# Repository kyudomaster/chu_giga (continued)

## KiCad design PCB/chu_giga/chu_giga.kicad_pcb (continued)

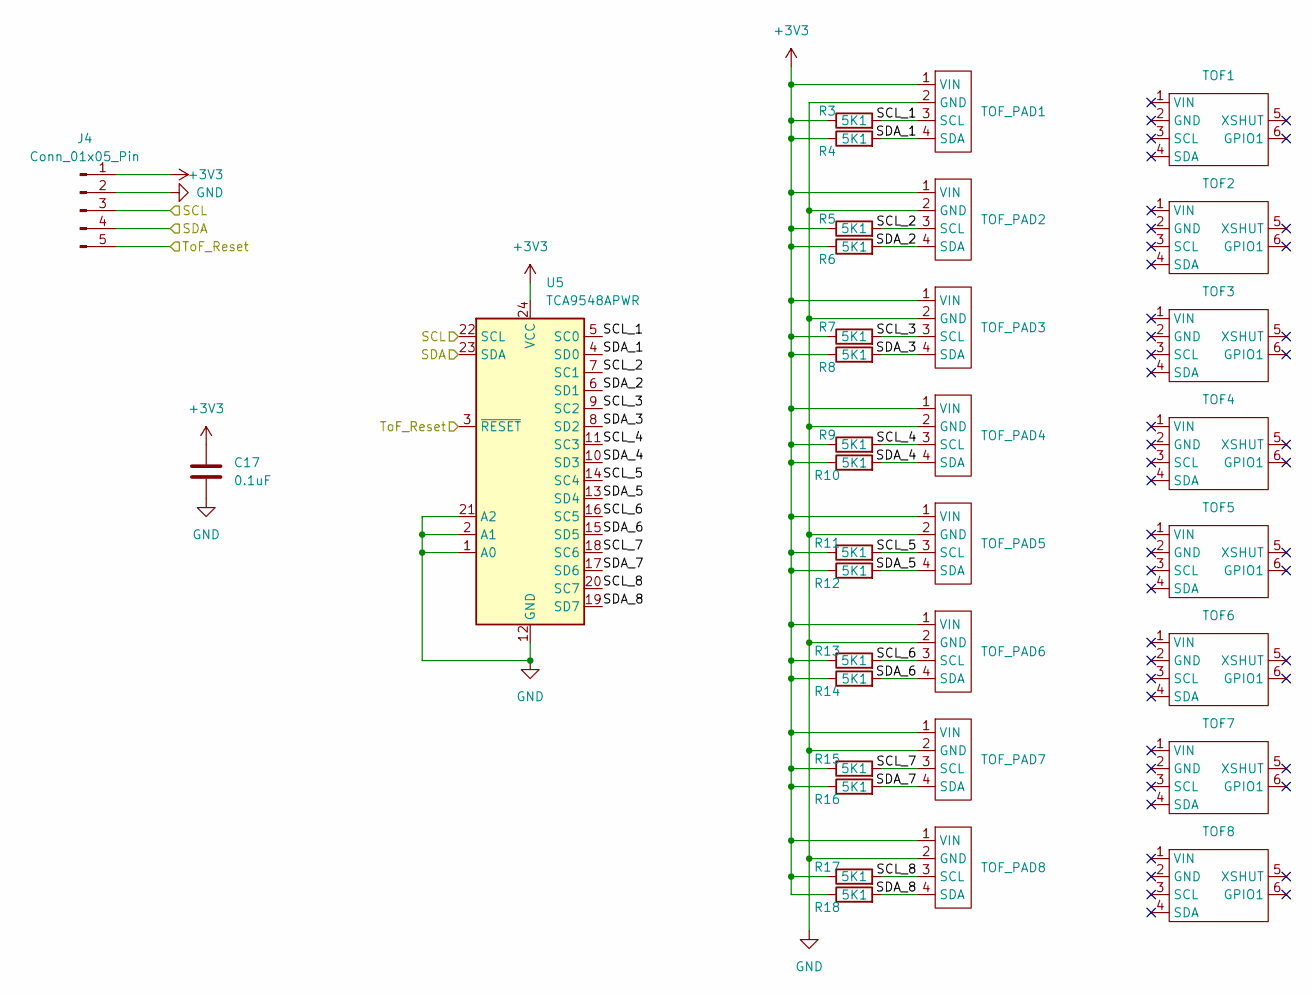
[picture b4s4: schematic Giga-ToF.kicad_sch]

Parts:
C17: 0.1uF; TMCP1E104MTRF
J4: Conn_01x05_Pin; 17754695
R3, R4, R5, R6, R7, R8, R9, R10, R11, R12, R13, R14, R15, R16, R17, R18: 5K1; R_0805_2012Metric_Pad1.20x1.40mm_HandSolder
TOF1, TOF2, TOF3, TOF4, TOF5, TOF6, TOF7, TOF8: GY530 ToF Sensor board
TOF_PAD1, TOF_PAD2, TOF_PAD3, TOF_PAD4, TOF_PAD5, TOF_PAD6, TOF_PAD7, TOF_PAD8: ToF Wiring Pad
U5: TCA9548APWR; SOP65P640X120-24N

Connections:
+3V3: C17.1, J4.1, R3.1, R4.1, R5.1, R6.1, R7.1, R8.1, R9.1, R10.1, R11.1, R12.1, R13.1, R14.1, R15.1, R16.1, R17.1, R18.1, TOF_PAD1.1 (VIN), TOF_PAD2.1 (VIN), TOF_PAD3.1 (VIN), TOF_PAD4.1 (VIN), TOF_PAD5.1 (VIN), TOF_PAD6.1 (VIN), TOF_PAD7.1 (VIN), TOF_PAD8.1 (VIN), U5.24 (VCC); also elsewhere on the board
/Controller/SCL: J4.3, U5.22 (SCL); also elsewhere on the board
/Controller/SDA: J4.4, U5.23 (SDA); also elsewhere on the board
/Controller/ToF_Reset: J4.5, U5.3 (~RESET); also elsewhere on the board
/Time-Of-Flight sensors/SCL_1: R3.2, TOF_PAD1.3 (SCL), U5.5 (SC0)
/Time-Of-Flight sensors/SCL_2: R5.2, TOF_PAD2.3 (SCL), U5.7 (SC1)
/Time-Of-Flight sensors/SCL_3: R7.2, TOF_PAD3.3 (SCL), U5.9 (SC2)
/Time-Of-Flight sensors/SCL_4: R9.2, TOF_PAD4.3 (SCL), U5.11 (SC3)
/Time-Of-Flight sensors/SCL_5: R11.2, TOF_PAD5.3 (SCL), U5.14 (SC4)
/Time-Of-Flight sensors/SCL_6: R13.2, TOF_PAD6.3 (SCL), U5.16 (SC5)
/Time-Of-Flight sensors/SCL_7: R15.2, TOF_PAD7.3 (SCL), U5.18 (SC6)
/Time-Of-Flight sensors/SCL_8: R17.2, TOF_PAD8.3 (SCL), U5.20 (SC7)
/Time-Of-Flight sensors/SDA_1: R4.2, TOF_PAD1.4 (SDA), U5.4 (SD0)
/Time-Of-Flight sensors/SDA_2: R6.2, TOF_PAD2.4 (SDA), U5.6 (SD1)
/Time-Of-Flight sensors/SDA_3: R8.2, TOF_PAD3.4 (SDA), U5.8 (SD2)
/Time-Of-Flight sensors/SDA_4: R10.2, TOF_PAD4.4 (SDA), U5.10 (SD3)
/Time-Of-Flight sensors/SDA_5: R12.2, TOF_PAD5.4 (SDA), U5.13 (SD4)
/Time-Of-Flight sensors/SDA_6: R14.2, TOF_PAD6.4 (SDA), U5.15 (SD5)
/Time-Of-Flight sensors/SDA_7: R16.2, TOF_PAD7.4 (SDA), U5.17 (SD6)
/Time-Of-Flight sensors/SDA_8: R18.2, TOF_PAD8.4 (SDA), U5.19 (SD7)
GND: C17.2, J4.2, TOF_PAD1.2 (GND), TOF_PAD2.2 (GND), TOF_PAD3.2 (GND), TOF_PAD4.2 (GND), TOF_PAD5.2 (GND), TOF_PAD6.2 (GND), TOF_PAD7.2 (GND), TOF_PAD8.2 (GND), U5.1 (A0), U5.2 (A1), U5.12 (GND), U5.21 (A2); also elsewhere on the board

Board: 2 copper layers, 129 parts (12 on the bottom side), 95 nets, no tracks yet.

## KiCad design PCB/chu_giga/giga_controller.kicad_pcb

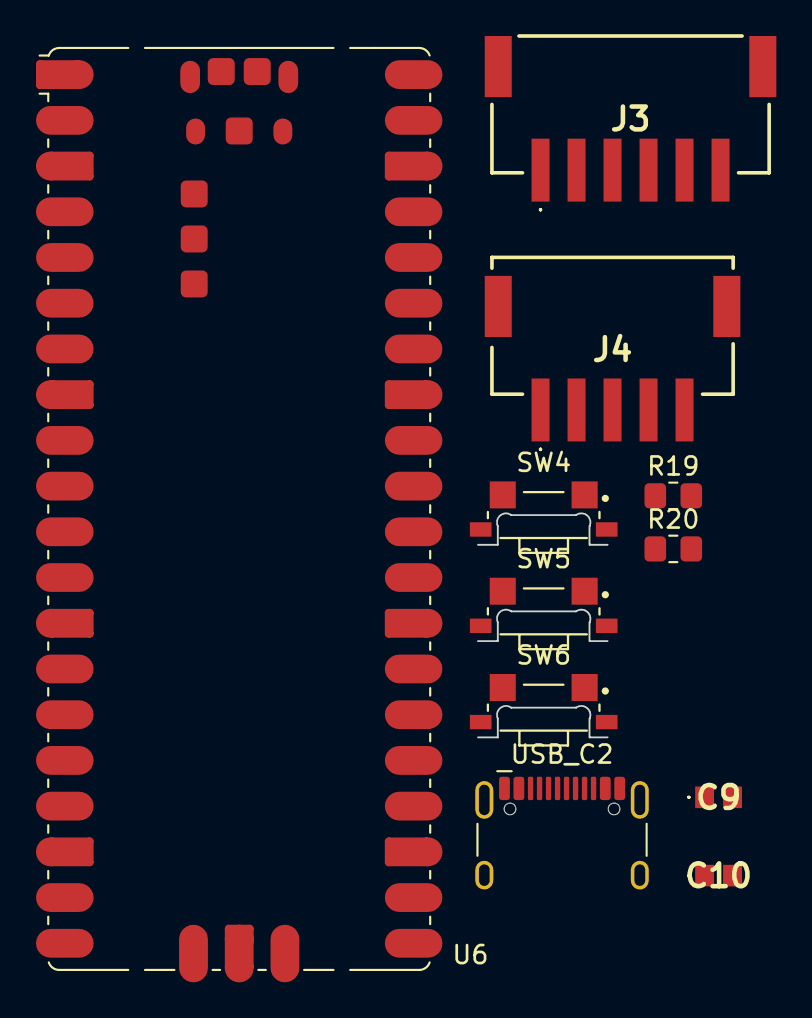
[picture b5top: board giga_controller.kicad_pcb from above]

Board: 2 copper layers, 11 parts (0 on the bottom side), 15 nets, no tracks yet.

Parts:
C9, C10: 0.1uF; TMCP1E104MTRF
J3: Conn_01x06_Pin; 17754696
J4: Conn_01x05_Pin; 17754695
R19, R20: 5K1; R_0805_2012Metric_Pad1.20x1.40mm_HandSolder
SW4, SW5, SW6: SW_SPST; SW_EVQ-P46B3M
U6: RaspberryPi_Pico_Testing_pins; RaspberryPi_Pico_SMD
USB_C2: USB_C_Receptacle_HCTL_HC-TYPE-C-16P-01A

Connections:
+3V3: C10.1, J3.3, J4.1, U6.36 (3V3)
+5V: C9.1, J3.2, U6.39 (VSYS)
/Controller/LED_Data: J3.4, U6.4 (GPIO2)
/Controller/SCL: J3.6, J4.3, U6.22 (GPIO17)
/Controller/SDA: J3.5, J4.4, U6.21 (GPIO16)
/Controller/ToF_Reset: J4.5, U6.25 (GPIO19)
GND: C9.2, C10.2, J3.1, J4.2, R19.2, R20.2, SW4.2 (B), SW5.2 (B), SW6.2 (B), U6.3 (GND), U6.8 (GND), U6.13 (GND), U6.18 (GND), U6.23 (GND), U6.28 (GND), U6.33 (AGND), U6.38 (GND), U6.TP1 (USB_GND), USB_C2.1 (GND), USB_C2.12 (GND), USB_C2.13 (SHIELD)
unnamed: SW4.1 (A), U6.20 (GPIO15)
unnamed: SW5.1 (A), U6.19 (GPIO14)
unnamed: SW6.1 (A), U6.17 (GPIO13)
unnamed: U6.TP2 (USB_DM), USB_C2.5 (DN2), USB_C2.7 (DN1)
unnamed: U6.TP3 (USB_DP), USB_C2.6 (DP1), USB_C2.8 (DP2)
unnamed: R20.1, USB_C2.4 (CC1)
unnamed: R19.1, USB_C2.10 (CC2)
VBUS: U6.40 (VBUS), USB_C2.2 (VBUS), USB_C2.11 (VBUS)

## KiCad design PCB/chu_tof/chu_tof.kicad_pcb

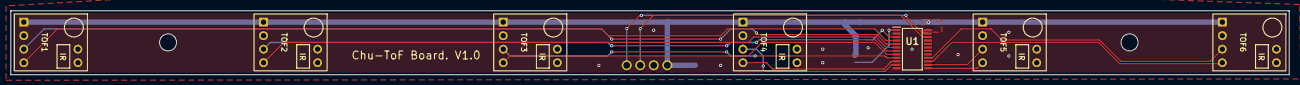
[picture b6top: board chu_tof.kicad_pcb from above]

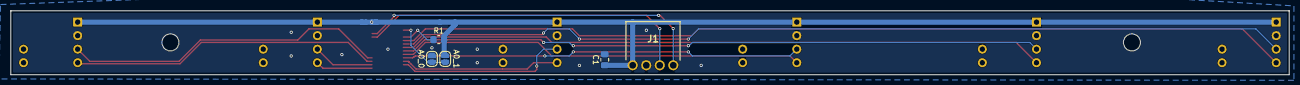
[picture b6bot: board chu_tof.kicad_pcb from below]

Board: 2 copper layers, 240.0 x 12.0 mm, 14 parts (5 on the bottom side), 18 nets.

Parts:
A0_0, A0_1: SolderJumper_2_Open; SolderJumper-2_P1.3mm_Open_RoundedPad1.0x1.5mm
C1: 1uF; C_0805_2012Metric_Pad1.18x1.45mm_HandSolder
J1: Conn_01x04_Pin; 6404554
R1: 5K1; R_0805_2012Metric_Pad1.20x1.40mm_HandSolder
SCR1, SCR2: MountingHole_3.2mm_M3
TOF1, TOF2, TOF3, TOF4, TOF5, TOF6: GY530 ToF Sensor board
U1: TCA9548APWR; SOP65P640X120-24N

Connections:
+3V3: A0_1.2 (B), C1.1, J1.1, R1.1, TOF1.1 (VIN), TOF2.1 (VIN), TOF3.1 (VIN), TOF4.1 (VIN), TOF5.1 (VIN), TOF6.1 (VIN), U1.24 (VCC)
/SCL: J1.3, U1.22 (SCL)
/SCL_1: TOF1.3 (SCL), U1.5 (SC0)
/SCL_2: TOF2.3 (SCL), U1.7 (SC1)
/SCL_3: TOF3.3 (SCL), U1.9 (SC2)
/SCL_4: TOF4.3 (SCL), U1.11 (SC3)
/SCL_5: TOF5.3 (SCL), U1.14 (SC4)
/SCL_6: TOF6.3 (SCL), U1.16 (SC5)
/SDA: J1.4, U1.23 (SDA)
/SDA_1: TOF1.4 (SDA), U1.4 (SD0)
/SDA_2: TOF2.4 (SDA), U1.6 (SD1)
/SDA_3: TOF3.4 (SDA), U1.8 (SD2)
/SDA_4: TOF4.4 (SDA), U1.10 (SD3)
/SDA_5: TOF5.4 (SDA), U1.13 (SD4)
/SDA_6: TOF6.4 (SDA), U1.15 (SD5)
GND: A0_0.1 (A), C1.2, J1.2, TOF1.2 (GND), TOF2.2 (GND), TOF3.2 (GND), TOF4.2 (GND), TOF5.2 (GND), TOF6.2 (GND), U1.2 (A1), U1.12 (GND), U1.21 (A2)
unnamed: A0_0.2 (B), A0_1.1 (A), U1.1 (A0)
unnamed: R1.2, U1.3 (~RESET)

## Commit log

2026-06-13 Create LICENSE
2026-06-13 Updated the readme and made some empty docs files to get started with.
2026-06-13 Restructured the docs a bit, all empty still.
2026-06-14 Wrote a system overview
2026-06-14 Changed Docs structure some and made some headers.
2026-06-14 Wrote a draft for the firmware architecture.
2026-06-14 More documentation stuff.
2026-06-15 TinyUSB test.
2026-06-16 One ToF array working :)
2026-06-17 more workinging Air boards, two of them now. Kinda broken but probably wiring or components.
2026-06-20 Working slider :)
2026-06-22 Dll progress.
2026-06-22 PCB and CAD file update.
2026-06-23 Increased max height.
2026-06-23 Removed button stay alive counting.
2026-06-25 updated air to be better
